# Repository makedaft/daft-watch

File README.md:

# Watch with attiny84a
My attempt at making a digital watch with attiny84a

### Schematic

### Inspiration
https://github.com/ingepnet/breadboardwatch

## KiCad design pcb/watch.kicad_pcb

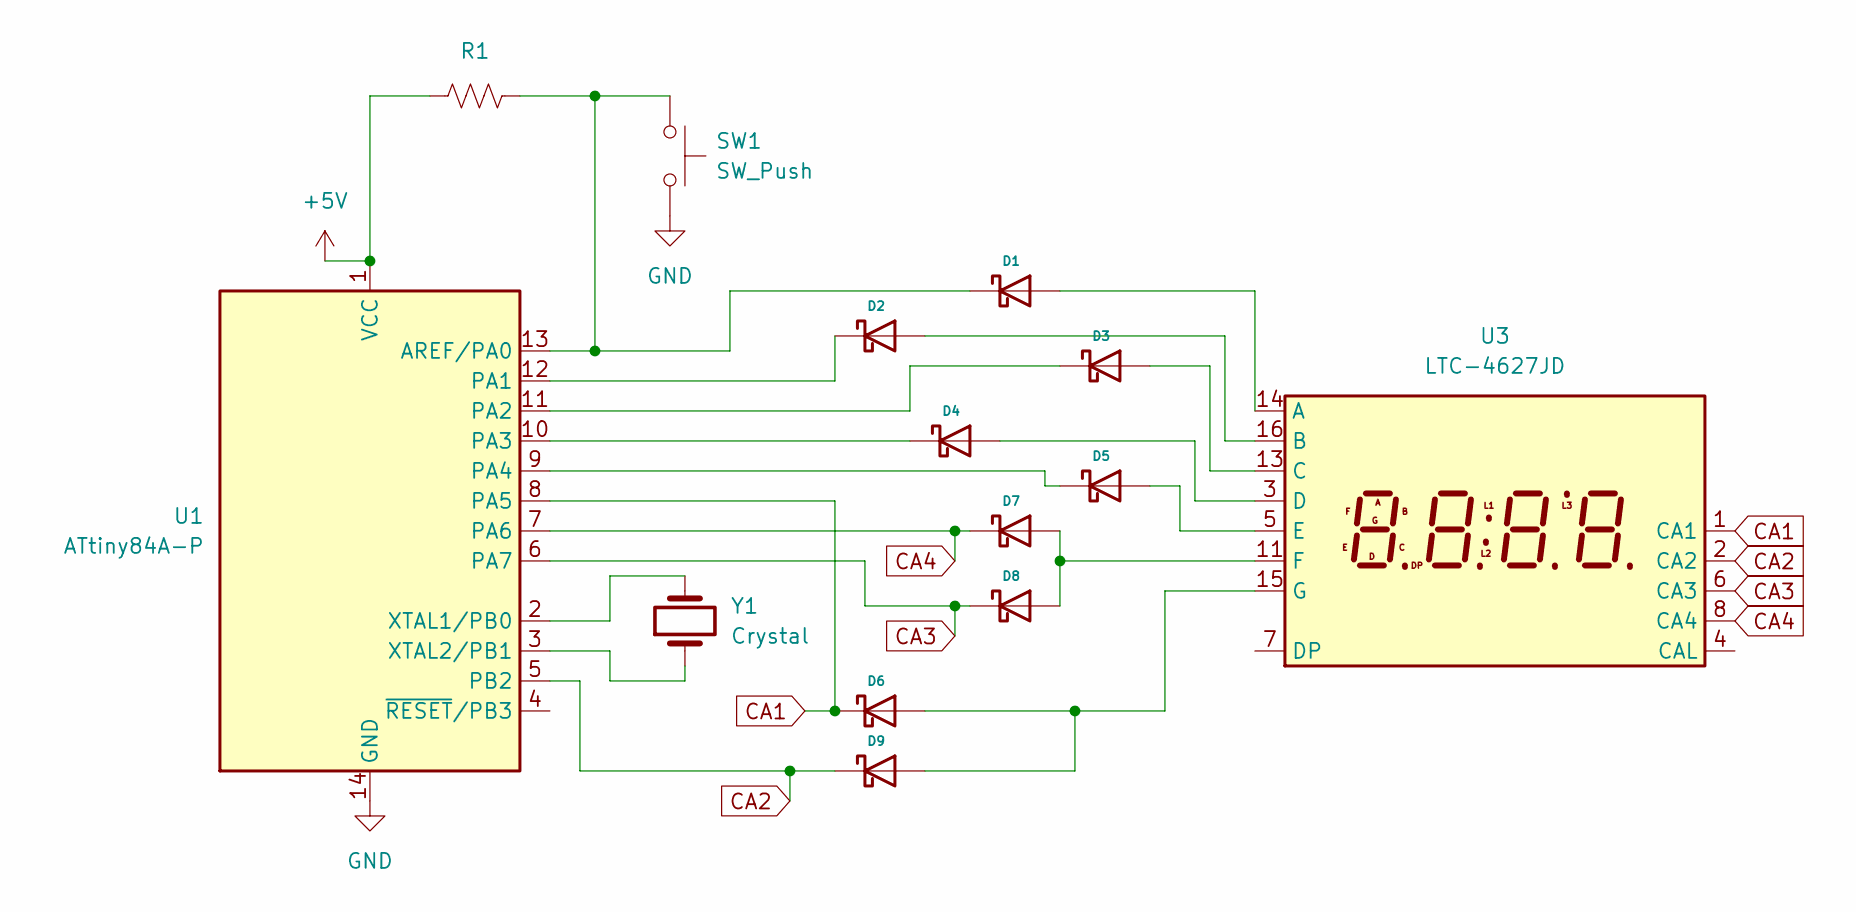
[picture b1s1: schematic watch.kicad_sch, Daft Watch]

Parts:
D1, D2, D3, D4, D5, D6, D7, D8, D9: 1N5819; D_DO-41_SOD81_P10.16mm_Horizontal
R1: R_US; R_Axial_DIN0207_L6.3mm_D2.5mm_P7.62mm_Horizontal
SW1: SW_Push; SW_PUSH_6mm
U1: ATtiny84A-P; DIP-14_W7.62mm
U3: LTC-4627JD; LTC-4627Jx
Y1: Crystal; Crystal_Round_D1.5mm_Vertical

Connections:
+5V: R1.1, U1.1 (VCC)
CA1: D6.1 (K), U1.8 (PA5), U3.1 (CA1)
CA2: D9.1 (K), U1.5 (PB2), U3.2 (CA2)
CA3: D8.1 (K), U1.6 (PA7), U3.6 (CA3)
CA4: D7.1 (K), U1.7 (PA6), U3.8 (CA4)
GND: SW1.2, U1.14 (GND)
unnamed: D1.2 (A), U3.14 (A)
unnamed: D1.1 (K), R1.2, SW1.1, U1.13 (AREF/PA0)
unnamed: D2.2 (A), U3.16 (B)
unnamed: D2.1 (K), U1.12 (PA1)
unnamed: D3.2 (A), U3.13 (C)
unnamed: D3.1 (K), U1.11 (PA2)
unnamed: D4.2 (A), U3.3 (D)
unnamed: D4.1 (K), U1.10 (PA3)
unnamed: D5.2 (A), U3.5 (E)
unnamed: D5.1 (K), U1.9 (PA4)
unnamed: D6.2 (A), D9.2 (A), U3.15 (G)
unnamed: D7.2 (A), D8.2 (A), U3.11 (F)
unnamed: U1.2 (XTAL1/PB0), Y1.2
unnamed: U1.3 (XTAL2/PB1), Y1.1

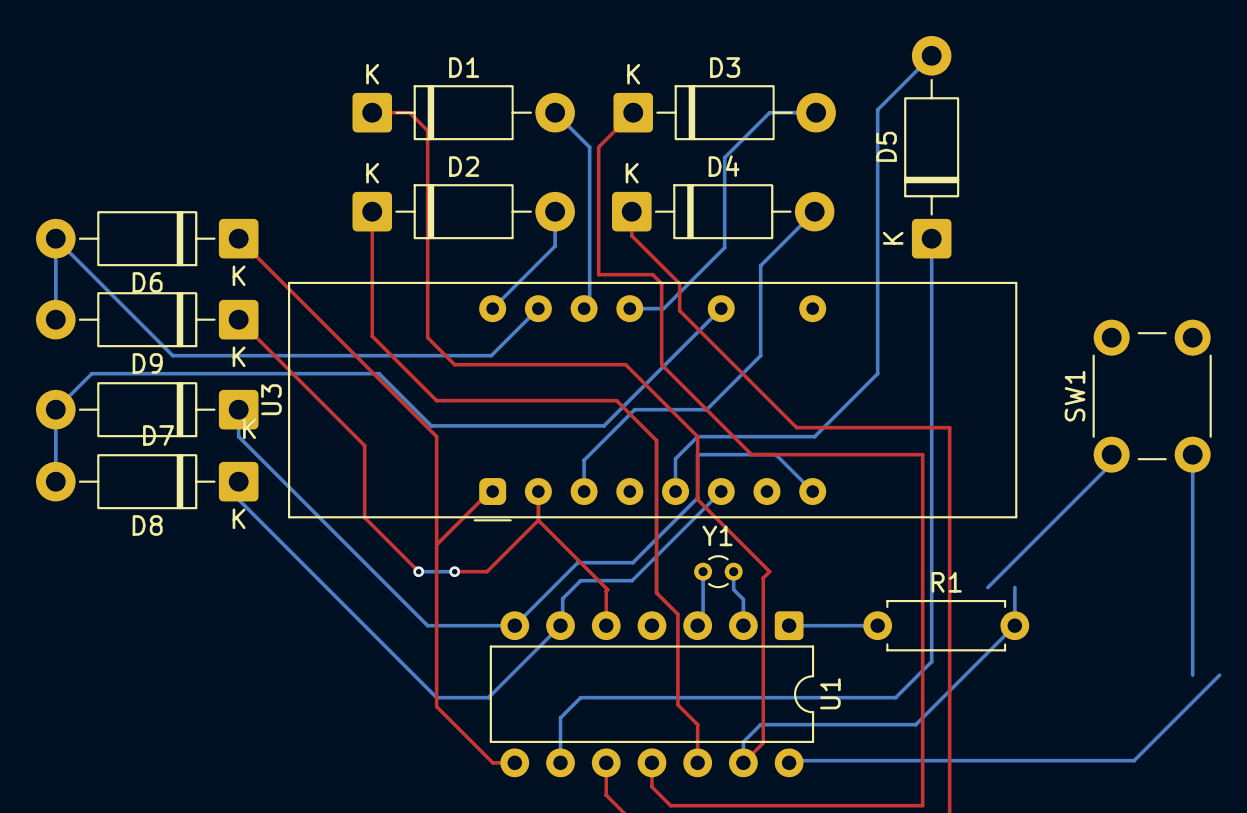
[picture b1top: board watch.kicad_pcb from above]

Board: 2 copper layers, 14 parts (0 on the bottom side), 20 nets.

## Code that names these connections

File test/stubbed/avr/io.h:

#ifndef STUB_AVR_IO
#define STUB_AVR_IO
#include <stdio.h>

extern int DDRA;
extern int DDRB;

extern int PORTA;
extern int PORTB;
extern int PINA;
extern int PINB;

#define PA0 0
#define PA1 1
#define PA2 2
#define PA3 3
#define PA4 4
#define PA5 5
#define PA6 6
#define PA7 7

#define PB1 1
#define PB2 2
#define PB3 3
#define PB4 4

extern int PRR;
extern int TCCR0B;
extern int TCCR0A;
extern int TIMSK0;
extern int TIFR0;
extern int OCR0A;
extern int OCR0B;
extern int TCNT0;
extern int TCCR1B;
extern int TCCR1A;
extern int TIMSK1;
extern int TIFR1;
extern int OCR1A;
extern int OCR1B;
extern int TCNT1;
extern int TCNT1H;
extern int TCNT1L;

#define CS00 1
#define CS01 1
#define CS02 2
#define CS10 1
#define CS11 1
#define CS12 2
#define WGM00 0
#define WGM01 1
#define WGM02 2
#define WGM10 0
#define WGM11 1
#define WGM12 2
#define WGM13 3
#define TOIE0 0
#define TOIE1 0
#define TOV0 0
#define TOV1 0
#define OCF1A 0
#define OCF1B 0
#define OCF0A 0
#define OCF0B 0
#define OCIE0A 0
#define OCIE0B 0
#define OCIE1A 0
#define OCIE1B 0
#endif

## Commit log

2026-01-31 Init commit with blink shit
2026-02-01 Remove platformio stuff and switch to avr-gcc
2026-02-02 Finished counter + digit display
2026-02-02 2 digit counter display
2026-02-02 Add simple stubb for testing
2026-02-02 Add readme
2026-02-04 Switch from internal clock to crystal + button
2026-02-05 Updates stub
2026-02-06 Use timer interrupt for writing to display
2026-02-06 Fix timer interrupt priority + refactor
2026-02-08 Handle button state
2026-02-14 Switch to using 2 pin hack to conserve gpio pins
2026-02-15 Add the other digits and refactor the fancy 2 pin hack
2026-02-19 Optimize display write
2026-02-27 Add kicad project files
2026-02-27 Refactor button
2026-02-28 Add set time mode + test for button
2026-03-01 Add tests for mode state
2026-03-01 Update schematic diagram + readme
